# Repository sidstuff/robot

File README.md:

# Obstacle avoiding robot

A common type is the micromouse, a small robot which tries to solve a maze. I.e., it tries to reach the center of a maze made up of a 16×16 grid of cells, each 180 mm square with walls 50 mm high.

## Usage

Clone the repo and open with KiCAD.

## Schematic

## Parts

While picking parts, ensure that the voltage/current/power ratings of componenets are not exceeded. Also, lithium cells have a nominal voltage of 3.7V (although it can go up to 4.2V when fully charged, and can be discharged until 3V), so their batteries are going to be multiples of the same.

### Microcontroller – Teensy 4.0

https://www.pjrc.com/store/teensy40.html

The Teensy 4.0 is compatible with the Arduino software, smaller than the Nano, and more powerful than the Giga (2x the CoreMark score). It needs a 5V supply voltage, so we'll use a 3.7V Li-ion battery with A TPS61099x 5V boost converter.

#### Why not older models?

> PJRC recommends use of Teensy 4.0 / 4.1 for new projects. We do not believe supply of chips for Teensy 3.x is likely to ever fully recover. These chips are made with 90 nm silicon process. Most of the world's semiconductor fabs are focusing on 45 nm or smaller, leaving limited supply for older chips. We anticipate the cost of these chips is likely to increase as the supply continues to dwindle.
>
> www.pjrc.com/store/teensylc.html

Thus we use the 4.x series to future-proof our design. The 4.0 is the smaller model of the series and is sufficient for our project.

### Motors – N20 gear motors, driven by the L293D

We will use the common N20 gear motor. To pick the specifications of the same, let's make use of this [Drive Motor Sizing Tool](https://community.robotshop.com/blog/show/drive-motor-sizing-tool)
```
Total mass: 210g                 When picking components, we should keep the total weight at or below this.
Number of drive motors: 2        Each of the rear wheels will have a sepaarte motor, turning will be achieved by driving them at different speeds.
Radius of drive wheel: 32.5 mm   Use 65 mm RC wheels
Robot velocity: 1.35 m/s         Micromice can run at over three meters per second, depending on the maze design.
Maximum incline: 0 deg           A simple maze solving robot doesn't need to worry about performance climbing inclines.
Supply voltage: 12 V             12V is the highest available voltage for the N20. A higher voltage means less current/charge is required for the same power/energy output. 
Desired acceleration: 4 m/s2     Micromice can run with forward acceleration and braking well over 1g.
Total efficiency: 40%            N20 motors have a maximum efficiency of around 0.4
```
```
Angular Velocity: 396.86 rpm
Torque: 0.34786 kgf-cm
Total Power: 1.4175 W
Maximum current: 118.13 mA
```
The [N20 motor rated for 12V 400RPM](https://robu.in/product/n20-12v-400-rpm-micro-metal-gear-motor) fulfils these requirements. It has a rated torque of 0.35 kg-cm. The recommendation for brushed DC motor operation is 25% or less of the stall current. The stall current for the above motor is 0.75 A, and the required current of 118.13 mA is less than 16% of it.

Make sure to buy the version with a [motor encoder](https://www.pololu.com/product/5215) and [its wires](https://www.pololu.com/product/4762) – it tells us how much the motor has rotated and thus the robot's speed as well as the distance travelled.

With these motors, we will use a pair of [65mm RC wheels](https://srituhobby.com/product/65mm-rubber-wheel-rc-model-tire).

On the [L293D motor driver](https://www.electronicscomp.com/l293d-dual-h-bridge-motor-driver-ic), there are two pins to control the direction of each motor as follows:
| IN1	| IN2 |	Spinning Direction |
| --- | --- | --- |
| LOW | LOW| Motor OFF |
| HIGH	| LOW | Forward |
| LOW | HIGH | Backward |
| HIGH	| HIGH |	Motor OFF |

The enable pin for each motor can be used to switch it on/off (as well as control the speed using PWM) so the `LOW,LOW` and `HIGH,HIGH` configurations are not needed. As for the remaining two, we can save two digital pins (one per motor) by using a logic inverter. Thus we use the Dual Schmitt-Trigger Inverter, but since we have a pin to spare, we end up using a digital pin for the inverter supply voltage (instead of the 3.3V pin) to simplify the connections.

The L293D will drop the motor supply voltage by ~2.6V, so we will use a 14.8V LiPo battery for the motors.

### Accelerometer – ADXL345

Calculating the position of the robot from the rotation of the motor is complicated by turns of the robot, and some slipping can mess up the entire calculation thereafter. Thus we make use of an accelerometer.

### Gyroscope - MPU6050

Similarly, a gyroscope tells us how many degrees the robot has turned.

<table><td><b>NOTE</b>: Both the ADXL345 and the MPU6050 are I2C devices and thus we use 2.2k pull-up resistors on the SDA and SCL connections because the Teensy's internal pull-up resistors are too weak.</td></table>

### Distance sensors

Note that distance sensors have a dead zone or blanking distance of say, x cm, beginning from the face of the sensor and extending outward, within which it cannot measure distances. One can simply position the sensor x cm inwards on the robot if they wish to measure distances in that zone.

#### Front - Sharp GP2Y0A41SK0F

https://www.pololu.com/product/2464

The GP2Y0A41SK0F is an IR sensor with a range of 4 – 30 cm. Considering the size of the robot and its enclosings, this is a good range within which to detect obstacles so the robot can decide if and how much to speed up, slow down, or stop, and can do so in time. A simple calculation is that if the robot is moving at its maximum speed of 1.35 m/s and has a maximum acceleration (deceleration in this case) of 4 m/s2, it can come to a stop within a distance of v²/2a = 22.8 cm.

This sensor draws current in large, short bursts, which is why we should (and do) place a 10 µF capacitor or larger across the 5V supply and ground, close to the sensor.

The sensor will be stuck to the front of the robot and a [3-Pin Female JST-PH Cable with male pins](https://www.pololu.com/product/1799) will be used to connect it to 0.1" female pins on our PCB.

#### Sides – VL6180X

https://www.pololu.com/product/2489

The sides of the robot will approach closer to walls and obstacles than the front, so a shorter minimum range is required. The VL6180X is a time-of-flight ranging sensor with a range of 1 – 20 cm (or 60 cm with reduced resolution), which is sufficient. It uses 2.8V logic, so we use the LP5907MFX-2.8 linear voltage regulator to convert 3.3V to 2.8V.

It is an I2C device, and we use 10k pull-up resistors on the SDA and SCL connections. Its I2C address will reset to 0x29 when powered off and on again, so for simplicity, we let the two chips have identical addresses and instead connect them to different SDA/SCL pins on the microcontroller.

Each chip (with its associated componenets) will be on a separate board that will be stuck to the side of the robot, and connected to the main PCB via common 0.1" pins and jumper cables.

### RG bicolor LEDs – LTST-C235KGKRKT

We use voltage dividers to supply a fraction of the two batteries' voltages to analog pins on the Teensy. Based on these, the microcontroller can make two corresponding bicolor LEDs display hues from green to yellow to red, to indicate the charge. An LED can blink red when the level is danngerously low, and blink green when its corresponding battery is done charging. The LED is rated for 20mA but the Teensy's pins have a limit of 10mA. The voltage supplied to the LED will always be 3.3V, the brightness will be controlled using PWM. The LED forward voltage is 2V. Thus the value of the current limiting resistor used should be at least (3.3−2)/0.01 = 130 ohms, so let's use a standard 150 ohm resistor.

### Buzzer – AI-3035-TWT-3V-R

We can have the buzzer buzz at different frequencies and beep at different delays to notify us of various things. Its rating of 3V,9mA is within the limits of the Teensy pin. For every doubling of distance, the sound level reduces by 6dB, so its volume of 100dB@10cm means that our buzzer will have a nicely audible volume of 60dB 10m away.

<table><td><b>TODO</b>: Due to laziness, the PCB currently uses KiCAD's standard 12x9.5mm buzzer footprint, which should be replaced with a custom but more accurate 30x20mm one – this means the PCB will be larger than it currently is.</td></table>

### Potentiometer – RK09K or similar

We'll use a 10k rotary potentiometer (vertical) with a knob to provide an analog voltage that indicates the speed at which we want the robot to move.

### Switches

We need two switches. First, an SPST rocker switch connected (not on the PCB) to the 3.7V battery to just switch on the circuitry, perhaps to check the working status of the components, battery level, etc. Then a normally open SPST Push button switch, like the MEC 5GTH935, to signal that the robot should start moving. Normally the Teensy pin is pulled down to ground, but when the switch is pressed, it momentarily becomes HIGH, and upon receiving this signal, the microcontroller starts the robot's motion.

### 2 Pin Screw Terminals – Xinya XY308-2P 2.54MM

In total, we require five [2 pin screw terminals](https://www.tme.com/in/en/details/xy308-2p-2.54-gn/pcb-terminal-blocks/xinya/xy308-2p-2-54mm-green) to connect various unterminated wires to the PCB.

### Batteries

| Part | Weight (g) | Voltage (V) | Current (mA) |
| --- | --- | --- | --- |
| 1 x Teensy 4.0 | 2.8 | 5 | 100 |
| 2 x N20 | 12 | 14.8 | 118 |
| 2 x wheels | 31 | - | - |
| 1 x L293D | 2.1 | 5 | 24 |
| 1 x ADXL345 | 0.03 | 3.3 | 0.04 |
| 1 x MPU6050 | 0.03 | 3.3 | 3.6 |
| 1 x GP2Y0A41SK0F | 3.5 | 5 | 12 |
| 2 x VL6180X (with LP5907MFX) | 0.03 | 3.3 | 25 |
| 2 x (LTST-C235KGKRKT + 150ohm) | 0.04 | 3.3 | 8.67 |
| 1 x AI-3035-TWT-3V-R | 12 | 3 | 9* |
| 1 x RK09K | 4.5 | 3.3 | 0.33 |
| 1 x Rocker Switch | 1.4 | 0 | - |
| 1 x 5GTH935 | 3 | 3.3 | 0.7* |
| 5 x XY308-2.54 | 0.5 | 0 | - |

`*` – current flows rarely

Adding all the weights, we get 112g. For the batteries, let's pick the [3.7V 3.7Wh 1000mAh LiPo](https://www.lithium-polymer-battery.net/lp543450-3-7v-1000mah-3-7wh-lithium-polymer-battery)  (20g) and the [Orange 14.8V 360mAh 25C 4S LiPo](https://robu.in/product/orange-360mah-4s-25c-14-8-v-lithium-polymer-battery-pack-li-po) (60g). This brings the weight up to 192g, but this is excluding the PCB material, wires, connectors, and small circuit elements. A PCB weighs a couple grams per square inch – see [custompcb.com/faq.php](https://custompcb.com/faq.php) – so the final weight should come out to around 210g.

The 14.8V Lipo is 25C, so can deliver a maximum current of 0.36Ah * 25h^(-1) = 9A, which is more than enough for our motors. They draw upto 2 * 118mA = 236 mA, so our battery will last 360mAh / 236 mA = 1.5h, if the robot was continuously running at full power, but in reality, will last longer.

The following diagram shows the flow of current from the 3.7V LiPo.
```
------------------------------------ 3.7V
               |
      301.2 mA (1114.5 mW)
               |
      ----------------------
      | TPS61099 (93% eff) |
      ----------------------
               |
---------------|-------------------- 5V
               |
      207.3 mA (1036.5 mW)
               |
      -------------------
      |                 |
      |              171.3 mA
      |                 |
 --------------  -------|------------------
 | 5V Devices |  |      |                 |
 --------------  |  ----------            |
      |          |  | Teensy |            |
      |          |  ----------            |
    36 mA        |   |      |             |
      |          |   |   ---|--- 3.3V     |
      |          | 100mA    |             |
      |          |   |   ---------------- |
      |          |   |   | 3.3V Devices | |
      |          |   |   ---------------- |
      |          |   |      |             |
      |          ----|------|--------------
      |              |      |
      |              |    71.3 mA
      |              |      |
      V              V      V
------------------------------------ GND
```

The 3.7V LiPo has a max continuous discharge current of 1000 mA so it will be able to provide our required current of 301.2 mA. It is a 3.7 Wh battery, so it will last 3.7Wh/1114.5mW = 3.3h.

## PCB

For a 1 oz copper thickness PCB, KiCAD's default trace width of 0.200mm is sufficient for the amount of current in our circuit, and so are the default 0.6/0.3 mm vias. We must also make sure to maintain some clearance betweeen traces, to prevent crosstalk. The routing in our PCB is tight at places, which is why our ground plane is important in that it reduces crosstalk.

From Wikipedia:
>  When two traces run parallel, an electrical signal in one can be coupled into the other through electromagnetic induction by magnetic field lines from one linking the other; this is called crosstalk. When a ground plane layer is present underneath, it forms a transmission line with the trace. The oppositely-directed return currents flow through the ground plane directly beneath the trace. This confines most of the electromagnetic fields to the area near the trace and consequently reduces crosstalk.

<br>

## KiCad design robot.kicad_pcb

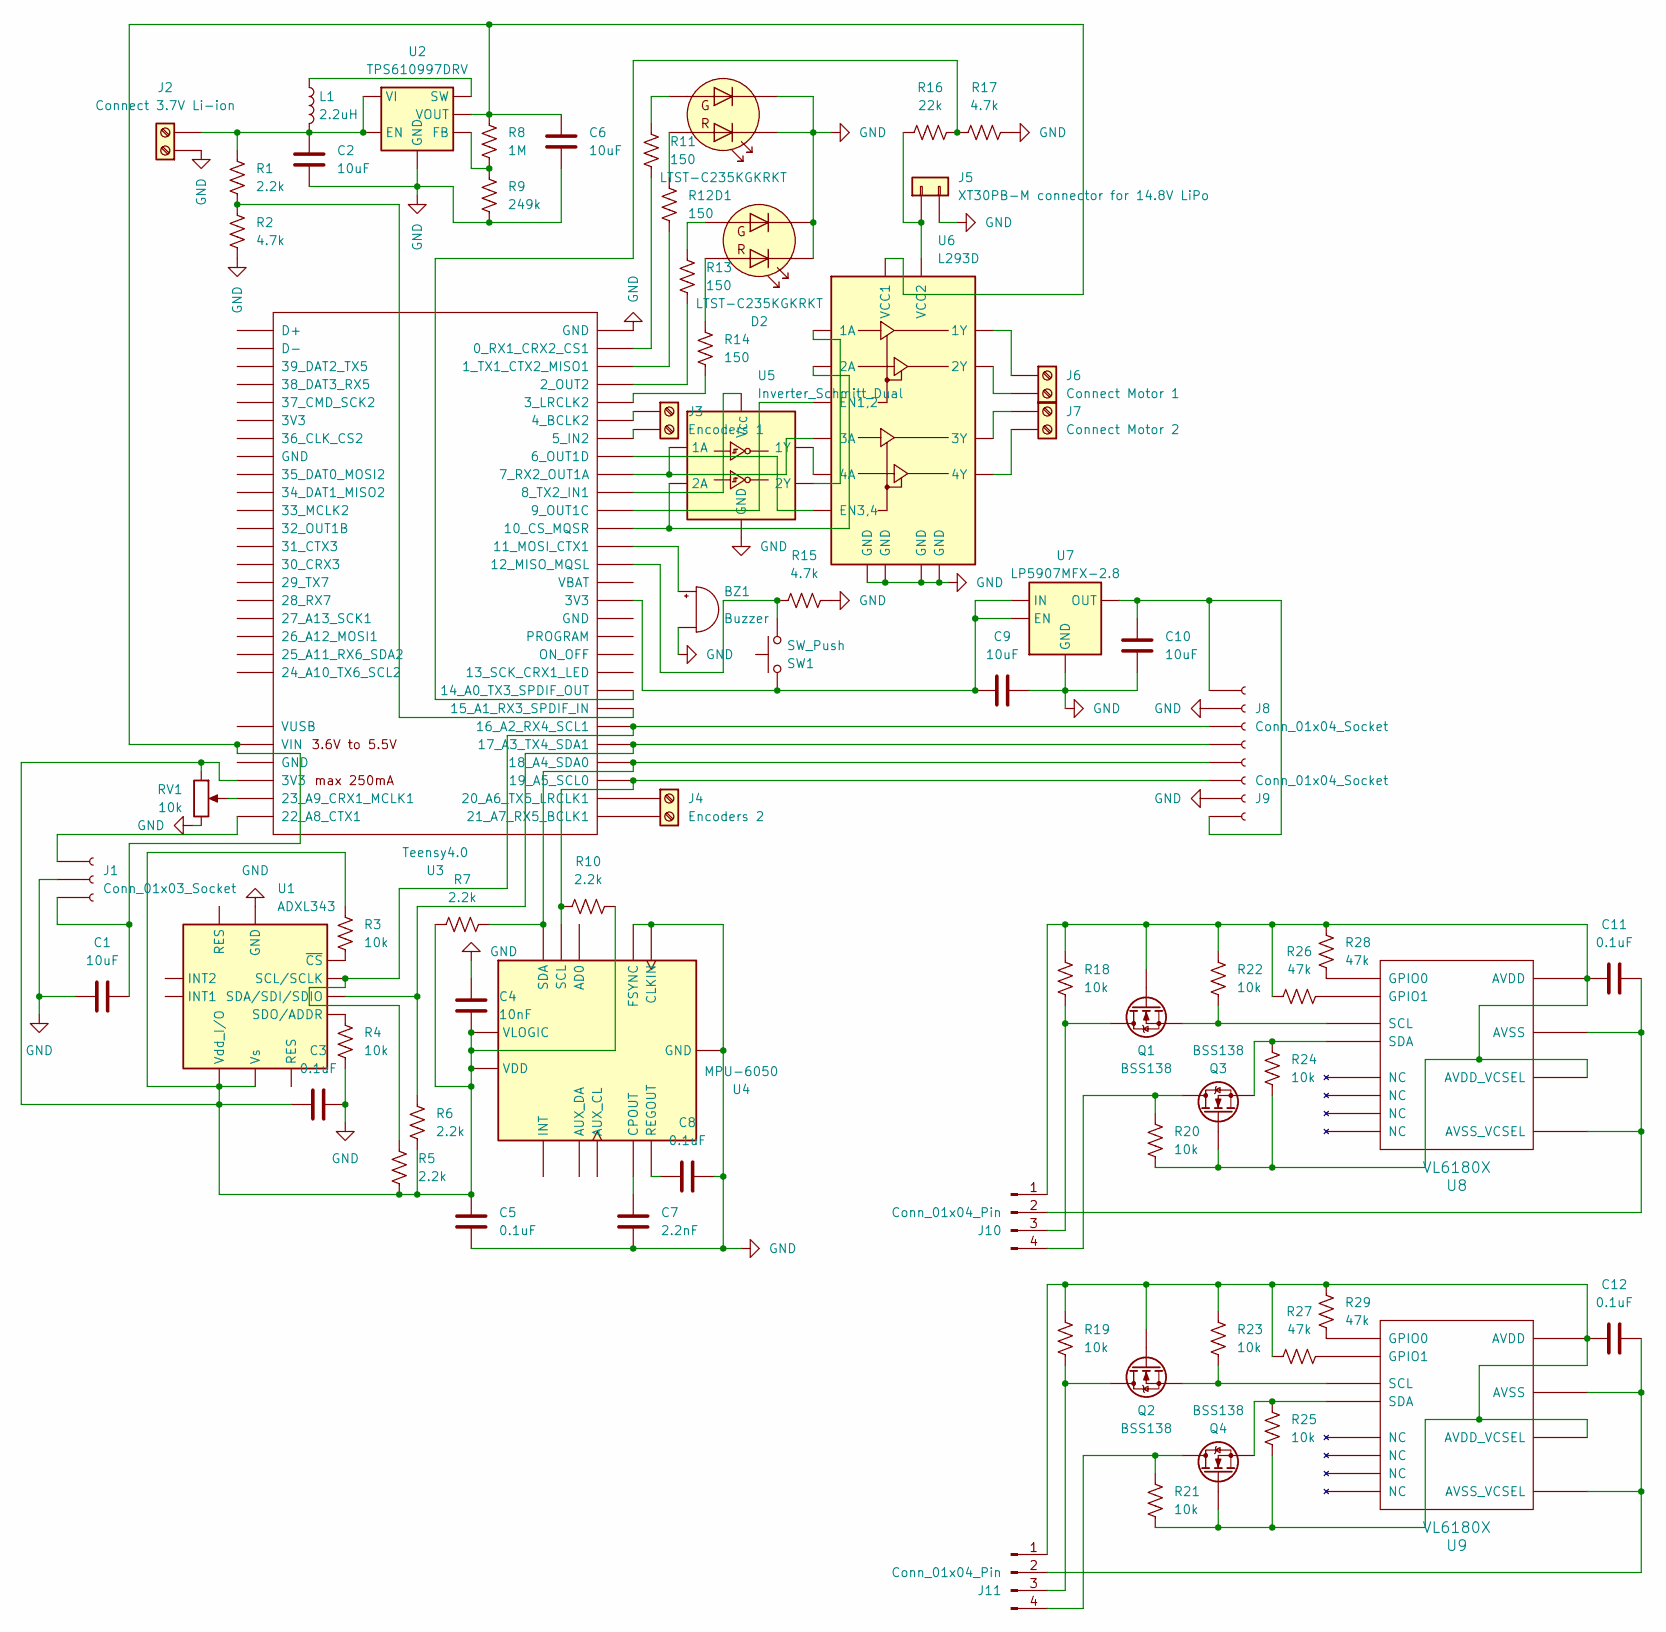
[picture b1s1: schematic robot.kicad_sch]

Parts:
BZ1: Buzzer; Buzzer_12x9.5RM7.6
C1, C2, C6, C9, C10: 10uF; C_0805_2012Metric
C3, C5, C8, C11, C12: 0.1uF; C_0402_1005Metric
C4: 10nF; C_0201_0603Metric
C7: 2.2nF; C_0201_0603Metric
D1, D2: LTST-C235KGKRKT; LED_LiteOn_LTST-C235KGKRKT
J1: Conn_01x03_Socket; PinSocket_1x03_P2.54mm_Vertical
J2: Connect 3.7V Li-ion; TerminalBlock_Xinya_XY308-2.54-2P_1x02_P2.54mm_Horizontal
J3: Encoders 1; TerminalBlock_Xinya_XY308-2.54-2P_1x02_P2.54mm_Horizontal
J4: Encoders 2; TerminalBlock_Xinya_XY308-2.54-2P_1x02_P2.54mm_Horizontal
J5: XT30PB-M connector for 14.8V LiPo; AMASS_XT30UPB-M_1x02_P5.0mm_Vertical
J6: Connect Motor 1; TerminalBlock_Xinya_XY308-2.54-2P_1x02_P2.54mm_Horizontal
J7: Connect Motor 2; TerminalBlock_Xinya_XY308-2.54-2P_1x02_P2.54mm_Horizontal
J8, J9: Conn_01x04_Socket; PinSocket_1x04_P2.54mm_Vertical
J10, J11: Conn_01x04_Pin; PinHeader_1x04_P2.54mm_Horizontal
L1: 2.2uH; L_1008_2520Metric
Q1, Q2, Q3, Q4: BSS138; SOT-23
R1, R5, R6, R7, R10: 2.2k; R_Axial_DIN0204_L3.6mm_D1.6mm_P5.08mm_Horizontal
R2, R15, R17: 4.7k; R_Axial_DIN0204_L3.6mm_D1.6mm_P5.08mm_Horizontal
R3, R4, R18, R19, R20, R21, R22, R23, R24, R25: 10k; R_Axial_DIN0204_L3.6mm_D1.6mm_P5.08mm_Horizontal
R8: 1M; R_Axial_DIN0204_L3.6mm_D1.6mm_P5.08mm_Horizontal
R9: 249k; R_Axial_DIN0204_L3.6mm_D1.6mm_P5.08mm_Horizontal
R11, R12, R13, R14: 150; R_Axial_DIN0204_L3.6mm_D1.6mm_P5.08mm_Horizontal
R16: 22k; R_Axial_DIN0204_L3.6mm_D1.6mm_P5.08mm_Horizontal
R26, R27, R28, R29: 47k; R_Axial_DIN0204_L3.6mm_D1.6mm_P5.08mm_Horizontal
RV1: 10k; Potentiometer_Alps_RK09K_Single_Vertical
SW1: SW_Push; SW_MEC_5GTH9
U1: ADXL343; LGA-14_3x5mm_P0.8mm_LayoutBorder1x6y
U2: TPS610997DRV; WSON-6-1EP_2x2mm_P0.65mm_EP1x1.6mm
U3: Teensy4.0; Teensy40_SMT
U4: MPU-6050; InvenSense_QFN-24_4x4mm_P0.5mm
U5: Inverter_Schmitt_Dual; SOT-363_SC-70-6
U6: L293D; DIP-16_W7.62mm
U7: LP5907MFX-2.8; SOT-23-5
U8, U9: VL6180X

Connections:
GND: BZ1.2 (-), C1.1, C2.1, C3.1, C4.1, C5.1, C6.1, C7.1, C8.1, C9.2, C10.1, D1.1 (K2), D1.4 (K1), D2.1 (K2), D2.4 (K1), J1.2, J2.1, J5.2, J8.2, J9.2, R2.1, R4.2, R9.2, R15.2, R17.2, RV1.3, U1.2 (GND), U1.4 (GND), U1.5 (GND), U2.1 (GND), U2.7 (GND), U3.1 (GND), U4.1 (CLKIN), U4.11 (FSYNC), U4.18 (GND), U5.2 (GND), U6.4 (GND), U6.5 (GND), U6.12 (GND), U6.13 (GND), U7.2 (GND)
unnamed: BZ1.1 (+), U3.13 (11_MOSI_CTX1)
unnamed: D1.3 (A1), R12.1
unnamed: D1.2 (A2), R11.1
unnamed: D2.3 (A1), R14.1
unnamed: D2.2 (A2), R13.1
unnamed: J1.1, U3.29 (22_A8_CTX1)
unnamed: C1.2, C6.2, J1.3, R8.1, U2.2 (VOUT), U3.33 (VIN), U6.16 (VCC1)
unnamed: C2.2, J2.2, L1.2, R1.2, U2.4 (EN), U2.6 (VI)
unnamed: J3.1, U3.6 (4_BCLK2)
unnamed: J3.2, U3.7 (5_IN2)
unnamed: J4.1, U3.27 (20_A6_TX5_LRCLK1)
unnamed: J4.2, U3.28 (21_A7_RX5_BCLK1)
unnamed: J5.1, R16.1, U6.8 (VCC2)
unnamed: J6.1, U6.3 (1Y)
unnamed: J6.2, U6.6 (2Y)
unnamed: J7.1, U6.11 (3Y)
unnamed: J7.2, U6.14 (4Y)
unnamed: C10.2, J8.1, J9.1, U7.5 (OUT)
unnamed: J8.3, R5.2, U1.14 (SCL/SCLK), U3.23 (16_A2_RX4_SCL1)
unnamed: J8.4, R6.2, U1.13 (SDA/SDI/SDIO), U3.24 (17_A3_TX4_SDA1)
unnamed: J9.3, R10.1, U3.26 (19_A5_SCL0), U4.23 (SCL)
unnamed: J9.4, R7.2, U3.25 (18_A4_SDA0), U4.24 (SDA)
unnamed: C11.1, J10.1, Q1.1 (G), Q3.1 (G), R18.1, R20.2, R22.1, R24.2, R26.1, R28.1, U8.8 (AVDD_VCSEL), U8.10 (AVDD)
unnamed: C11.2, J10.2, U8.9 (AVSS_VCSEL), U8.12 (AVSS)
unnamed: J10.3, Q1.3 (D), R18.2
unnamed: J10.4, Q3.3 (D), R20.1
unnamed: C12.1, J11.1, Q2.1 (G), Q4.1 (G), R19.1, R21.2, R23.1, R25.2, R27.1, R29.1, U9.8 (AVDD_VCSEL), U9.10 (AVDD)
unnamed: C12.2, J11.2, U9.9 (AVSS_VCSEL), U9.12 (AVSS)
unnamed: J11.3, Q2.3 (D), R19.2
unnamed: J11.4, Q4.3 (D), R21.1
unnamed: Q1.2 (S), R22.2, U8.5 (SCL)
unnamed: Q2.2 (S), R23.2, U9.5 (SCL)
unnamed: Q3.2 (S), R24.1, U8.6 (SDA)
unnamed: Q4.2 (S), R25.1, U9.6 (SDA)
unnamed: R4.1, U1.12 (SDO/ADDR)
unnamed: C3.2, C4.2, C5.2, R3.1, R5.1, R6.1, R7.1, R10.2, RV1.1, U1.1 (Vdd_I/O), U1.6 (Vs), U3.31 (3V3), U4.8 (VLOGIC), U4.13 (VDD)
unnamed: R3.2, U1.7 (~CS)
unnamed: R8.2, R9.1, U2.3 (FB)
unnamed: L1.1, U2.5 (SW)
unnamed: R11.2, U3.2 (0_RX1_CRX2_CS1)
unnamed: R12.2, U3.3 (1_TX1_CTX2_MISO1)
unnamed: R13.2, U3.4 (2_OUT2)
unnamed: R14.2, U3.5 (3_LRCLK2)
unnamed: U3.8 (6_OUT1D), U6.9 (EN3,4)
unnamed: U3.9 (7_RX2_OUT1A), U5.1 (1A), U6.10 (3A)
unnamed: U3.10 (8_TX2_IN1), U5.5 (V_{CC})
unnamed: U3.11 (9_OUT1C), U6.1 (EN1,2)
unnamed: U3.12 (10_CS_MQSR), U5.3 (2A), U6.7 (2A)
unnamed: R15.1, SW1.1, U3.14 (12_MISO_MQSL)
unnamed: R16.2, R17.1, U3.21 (14_A0_TX3_SPDIF_OUT)
unnamed: R1.1, R2.2, U3.22 (15_A1_RX3_SPDIF_IN)
unnamed: RV1.2, U3.30 (23_A9_CRX1_MCLK1)
unnamed: C7.2, U4.20 (CPOUT)
unnamed: C8.2, U4.10 (REGOUT)
unnamed: U5.6 (1Y), U6.15 (4A)
unnamed: U5.4 (2Y), U6.2 (1A)
unnamed: C9.1, SW1.2, U3.16 (3V3), U7.1 (IN), U7.3 (EN)
unnamed: R28.2, U8.4 (GPIO0)
unnamed: R26.2, U8.1 (GPIO1)
unnamed: R29.2, U9.4 (GPIO0)
unnamed: R27.2, U9.1 (GPIO1)

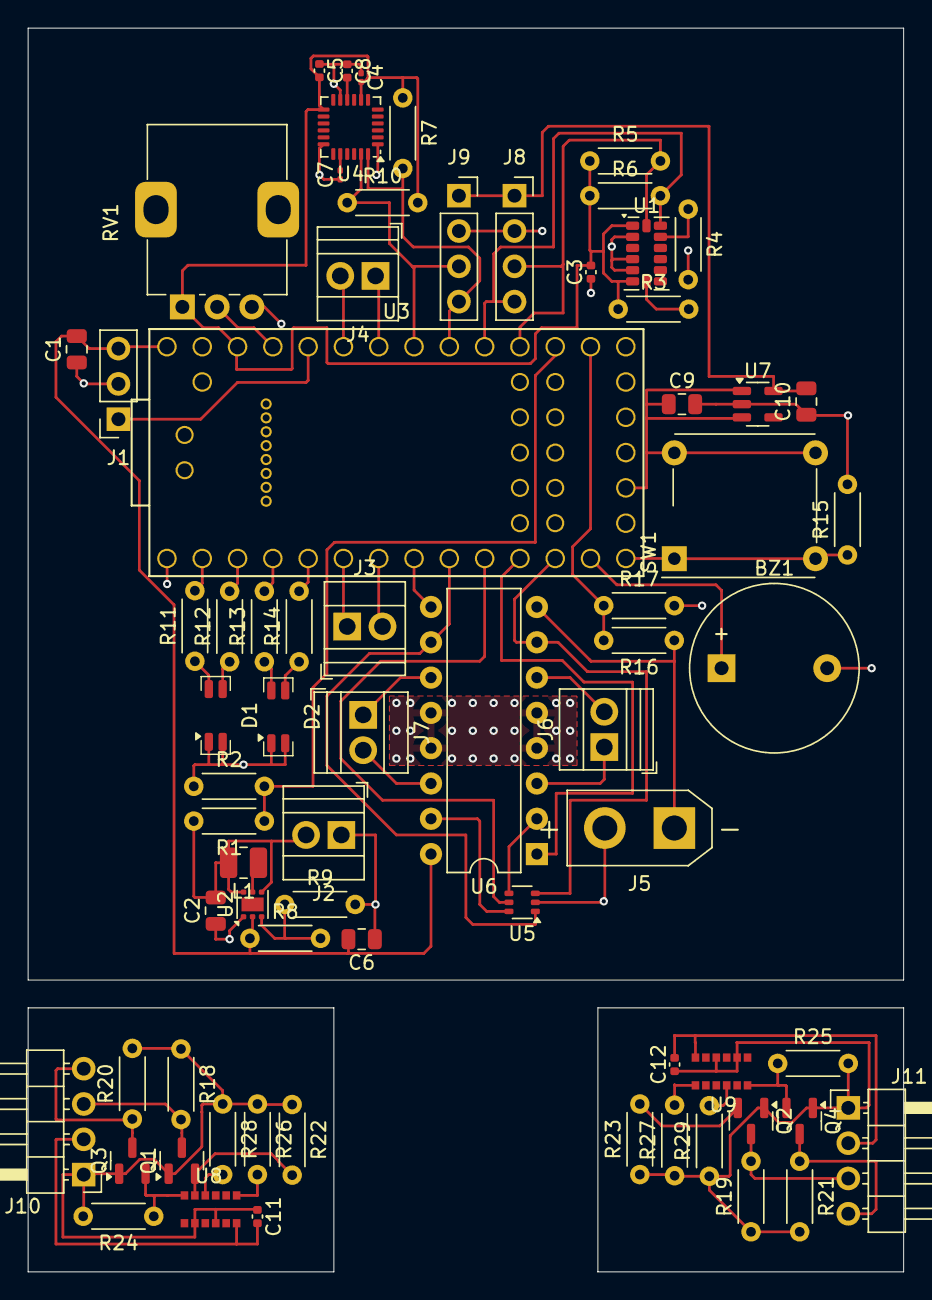
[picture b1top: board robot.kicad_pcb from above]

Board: 2 copper layers, 63.0 x 89.5 mm, 71 parts (0 on the bottom side), 62 nets.

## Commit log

2024-09-12 upload files
